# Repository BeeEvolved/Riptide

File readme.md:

```
Open Source is Intrinsic to Bitcoin
```
# The bitaxeUltra 204 Riptide
Riptide, an Ocean-themed Bitaxe.
### Future Riptide Design Goals
- LEDs around the edges to create a BitHalo effect, with the LEDs producing a blue swirl, riptide or waves effect.

bitaxe is a fully open source hardware Bitcoin ASIC miner. Ultra is the 3rd major revision of the bitaxe that now includes the BM1366 ASIC from the S19XP

## Goals
- **Standalone**: can mine directly to your pool over WiFi. No External computer needed.
- **Embedded**: low cost, low maintenance, high availability, high reliability, low power.
- **ASIC**: based on the very, very efficient BM1366 from Bitmain.
- **Versatile**: solo/pool mining, autotune power/heat/efficiency.
- **Open Source**: All design files are provided.

## Features
- **ESP32-S3-WROOM-1** wifi microcontroller on board
- **TI TPS40305** buck regulator steps down the 5V input to power the BM1366
- **Maxim DS4432U+** current DAC digitally adjusts the BM1366 core voltage from 0.04V to 2.4V
- **TI INA260** power meter measures the input voltage and current of the miner
- **Microchip EMC2101** PWM controls the fan and monitors tach output. BM1366 doesn't support die temp, but we have it placed super close to the ASIC so we can use the internal temp feature.
- 0.91" **SSD1306 OLED** I2C Display Module 

## BM1366
- The BM1366 is a undocumented SHA256 mining ASIC from Bitmain. It's used in the Antminer S19XP and the S19k Pro
- Bitmain claims the BM1366 has 0.021J/GH efficiency
- The BM1366 is available (new) for around $15 each in small quantities.
- The BM1366 has a different footprint and pinout from the BM1397 and BM1387 in previous bitaxe.
- The BM1366 appears to roll more than just the nonce on the chip. This is great news, because it allows much longer serial chains of ASICs and new work doesn't need to be sent as often.

## Current Status
- Bitaxe Ultra 204 hardware has been verified and is working nicely!
- Be sure to check the [issues](https://github.com/skot/bitaxe/issues) for known bugs, reworks and errata.
- This is an _advanced_ build! You can do it, but if you're not looking for a project, it might be best to buy one pre-assembled from one of the many sellers.

## Hardware
- Order PCBs from your favorite PCB shop, like [JLCPCB](https://jlcpcb.com), [SeeedStudio](https://www.seeedstudio.com/fusion_pcb.html), or [PCBWay](https://www.pcbway.com)
    - Gerbers are in the `Manufacturing Files` dir. PCBs are 4-layer, 6mil trace/space and 0.3mm hole compatible. 1oz outer / 0.5oz inner layer thickness works well.
    - Make sure to order stencils too. These are the "paste" layers in the gerbers folder. one for top and one for bottom.
- All PCB parts except the ASIC are available from [DigiKey](https://www.digikey.com/en/products) and others. You can find Digikey part numbers on the DK tab of the BOM
- [BM1366 ASIC from NBTC on AliExpress](https://www.aliexpress.us/item/3256804709142138.html). I got the "AG" variant. Not really sure what the difference is -- "AL" works also.
- [40x40mm heatsink and 5V fan](https://www.aliexpress.com/item/2251832861666365.html) from a random AliExpress seller. The fans are crap, but the heatsinks are good. **make sure** to use a good quality thermal compound between the heatsink and ASIC!
- Upgrade your fan with the [Noctua NF-A4x10](https://noctua.at/en/nf-a4x10-5v-pwm) 5V 4-Pin fan for a much more pleasant experience.
- Supports 0.91" SSD1306-based I2C OLED Module. [Example Amazon seller](https://www.amazon.com/gp/product/B08ZY4YBHL)
- [KiCad 7](https://www.kicad.org) design files

## Software
- The [ESP-Miner](https://github.com/skot/ESP-Miner) firmware used for the BM1397-based bitaxe has been adapted for the BM1366 and the current main branch can support both.

## Cooling
- You **must** have active cooling on the bitaxe. 
- The Bitaxe has a connector for a 5V fan. 40x40mm fans work nicely with the suggested heatsink
- The fan connector uses the 4-pin standard:
	- 2 pins are for 5V power
	- pin 3 is fan speed sensing
	- pin 4 is fan speed control (PWM) 

## Power Supply Requirements
- **5V DC Only!** Anything else will damage the Bitaxe. Be careful and double-check your power supply is 5V. Many other voltage power supplies use the same connector.
- [5VDC Power supply](https://www.amazon.com/BTF-LIGHTING-Plastic-Adapter-Transformer-WS2812B/dp/B01D8FM4N4). Should be capable of over 15W
- The bitaxe uses a 5.5x2.5mm, center-positive barrel jack.

### ESP32 Programming Requirements
- As of the bitaxeUltra, all ESP32 programming is done through a USB-C cable and connector on the bitaxe. See [ESP-Miner](https://github.com/skot/ESP-Miner) for more details.

## Building
- Check out [building.md](building.md) for PCB ordering tips
- Check out [assembly.md](assembly.md) for assembly tips

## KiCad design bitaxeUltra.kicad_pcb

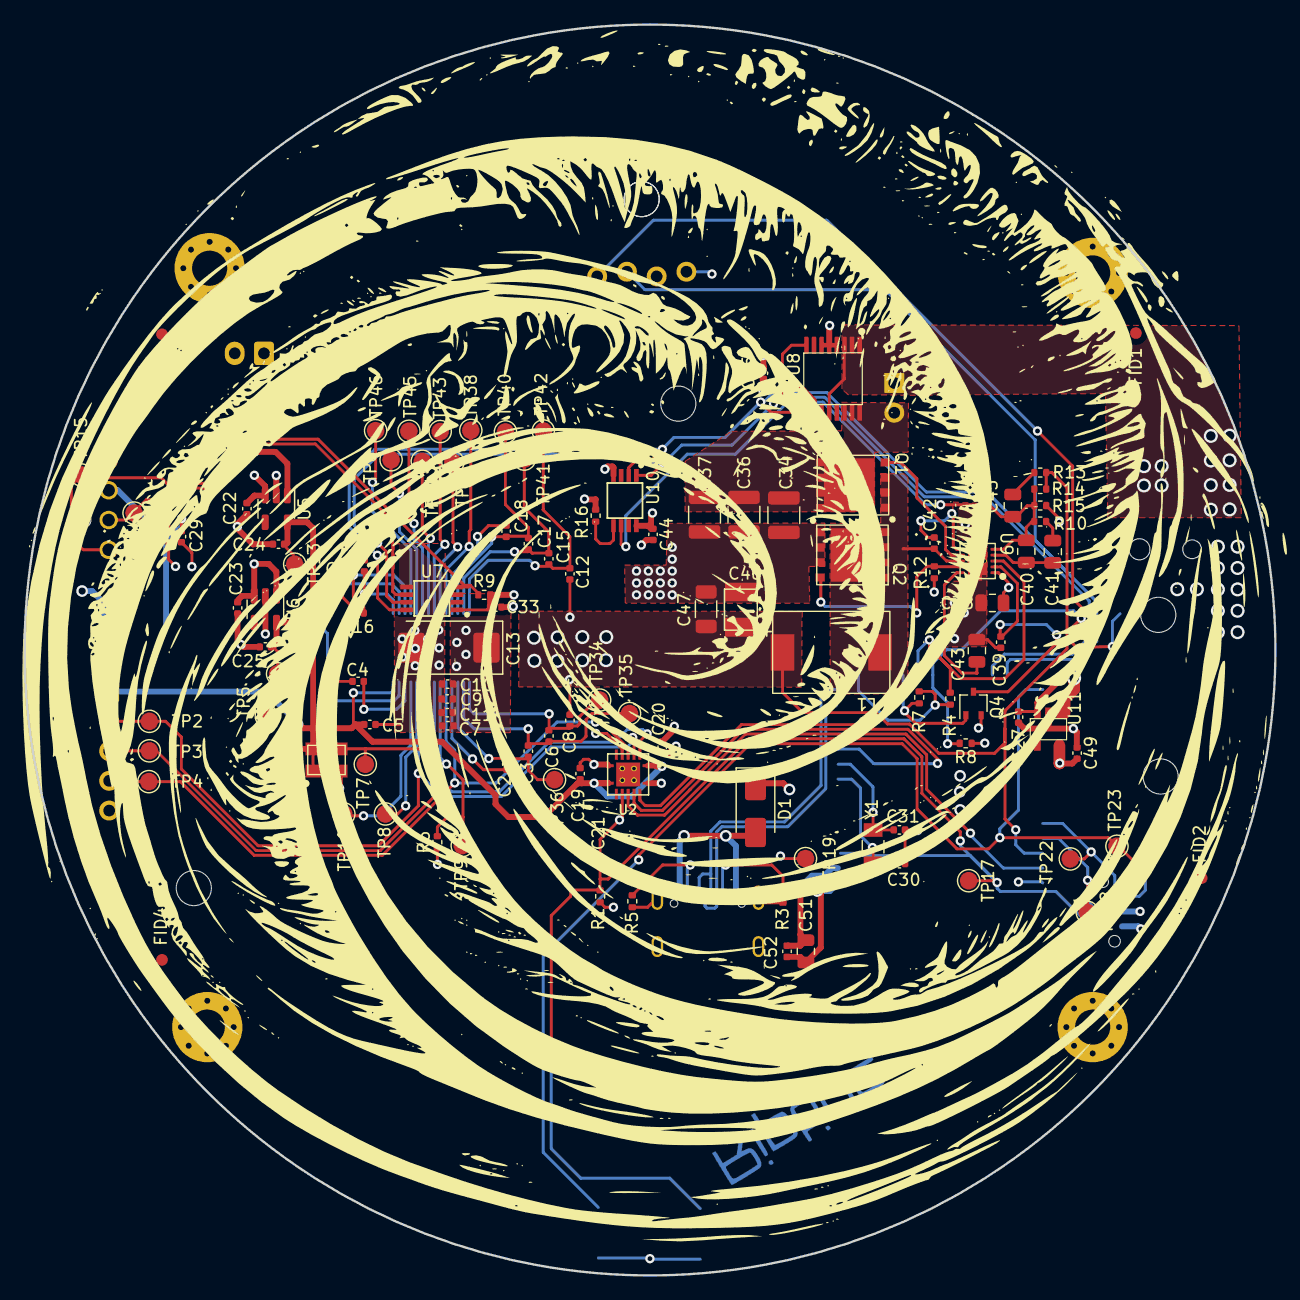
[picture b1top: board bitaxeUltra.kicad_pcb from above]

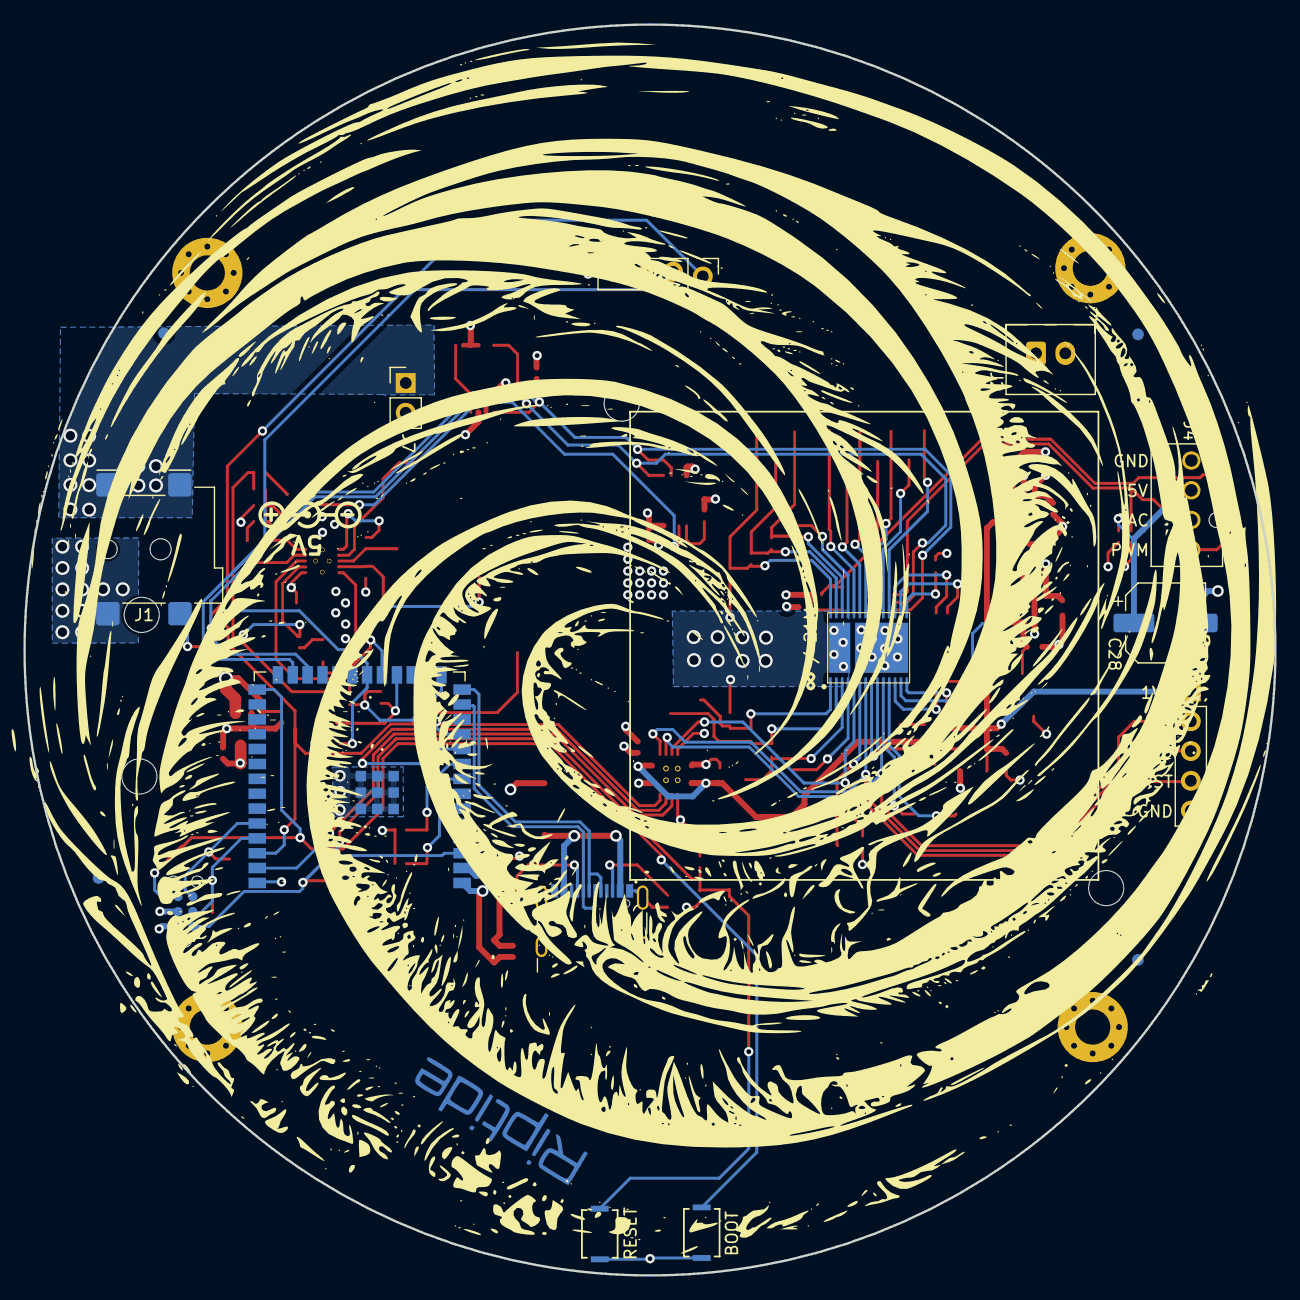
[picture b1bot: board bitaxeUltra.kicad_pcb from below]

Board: 4 copper layers, 106.8 x 106.8 mm, 135 parts (18 on the bottom side), 61 nets.

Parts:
C1, C7, C9, C19, C20, C29, C33, C42, C52: 0.1uF; C_0402_1005Metric
C2, C3, C4, C5, C6, C8, C10, C11, C12, C14, C15, C16, C17, C18, C21, C22, C23, C24, C25, C27, C35, C44, C49: 1uF; C_0402_1005Metric
C13: 330uF; CP_EIA-7343-31_Kemet-D_Pad2.25x2.55mm_HandSolder
C28: 220uF; CP_Elec_6.3x7.7
C30, C31: 6.8pF; C_0402_1005Metric
C34, C36, C37: 47uF; C_1210_3225Metric
C38: 1uF; C_0805_2012Metric
C39: 3.3nF; C_0402_1005Metric
C40: 180pF; C_0805_2012Metric
C41: 1.5nF; C_0805_2012Metric
C43, C51: 10uF; C_0805_2012Metric
C45: 470pF; C_0805_2012Metric
C46: 220uF; CAP_2R5TPE220MAFB
C47: 100uF; C_1206_3216Metric
D1: SS310; D_SMA
FID1, FID2, FID3, FID4, FID5, FID6, FID7, FID8: Fiducial; Fiducial_1mm_Mask2mm
H5, H6: MountingHole; MountingHole_3.5mm
H7, H8, H9, H10: MountingHole_Pad; MountingHole_3mm_Pad_Via
J1: 54-00164; BarrelJack_Wuerth_694106106102_2.0x5.5mm
J2: Conn_01x02; JST_XH_B2B-XH-A_1x02_P2.50mm_Vertical
J3: Conn_01x05; PinHeader_1x05_P2.54mm_Vertical
J3#2: Conn_01x04; PinHeader_1x04_P2.54mm_Vertical_shifted
J4: Conn_01x04; 470531000
J5: TC2030-IDC; Tag-Connect_TC2030-IDC-NL_2x03_P1.27mm_Vertical
J7: Conn_01x02; PinHeader_1x02_P2.54mm_Vertical
J8: USB_C_Receptacle_USB2.0; USB_C_Receptacle_GCT_USB4105-xx-A_16P_TopMnt_Horizontal
L1: 150nH; FP1005R1-R15-R
Q1, Q2: CSD17311Q5
Q4: 2N7002K; SOT-323_SC-70
R1, R4, R6, R7, R9: 10k; R_0402_1005Metric
R2: 5.6k; R_0402_1005Metric
R3, R5: 5.1k; R_0402_1005Metric
R8: 1M; R_0402_1005Metric
R10: 3.83k; R_0402_1005Metric
R12: 4.12k; R_0402_1005Metric
R13: 1.33k; R_0402_1005Metric
R14: 4.99k; R_0402_1005Metric
R15: 3.32k; R_0402_1005Metric
R16: 80.6k; R_0402_1005Metric
SW1, SW2: GT-TC029B-H025-L1N; SW_CS1213AGF260_CRS
TP1, TP2, TP3, TP4, TP5, TP6, TP7, TP8, TP9, TP10, TP13, TP14, TP15, TP16, TP17, TP18, TP19, TP22, TP23, TP34, TP35, TP36, TP38, TP40, TP41, TP42, TP43, TP44, TP45, TP46: TestPoint; TestPoint_Pad_D1.5mm
U1: 25MHz; O 25,0-JO32-B-1V3-1-T1-LF
U2: TXB0104RGYR; TXB0104
U3: polarity
U5: MCP1824T-1802E; SOT-23-5
U6: MCP1824T-0802E; SOT-23-5
U7: EMC2101; TSSOP-8_3x3mm_P0.65mm
U8: INA260; TSSOP-16_4.4x5mm_P0.65mm
U9: TPS40305
U10: DS4432U+; TSSOP-8_3x3mm_P0.65mm
U11: RT9080-33GJ5
U12: ESP32-S3-WROOM-1
U14: BM1366_mode1; BM1366
Y1: 32.768kHz; SC32S-7PF20PPM

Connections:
/3V3: C20.1, C33.1, C35.1, C44.1, C49.1, C51.1, C52.1, J3#2.3, J5.2, R1.1, R2.2, R4.1, R7.1, R8.1, R9.2, TP19.1, U2.14 (VCCB), U7.1 (VDD), U8.10 (VS), U10.8 (VCC), U11.5 (VOUT), U12.2 (3V3), U12.15 (GPIO3/TOUCH3/ADC1_CH2*)
/5V: C22.1, C23.1, C27.1, C28.1, C29.1, C34.1, C36.1, C37.1, C38.1, D1.1, J2.2, J4.2, J7.2, Q1.5 (D), U5.1 (VIN), U5.3 (EN), U6.1 (VIN), U6.3 (EN), U8.14 (IN-), U8.15 (IN-), U8.16 (IN-), U9.1 (VDD), U11.1 (VIN), U11.3 (EN)
/BM1366/0V8: C4.1, C25.1, TP14.1, U6.5 (VOUT), U14.13 (VDDIO_08_0)
/BM1366/1V8: C1.2, C5.1, C19.1, C24.1, J3.1, TP13.1, U1.1 (EN), U1.4 (VIN), U2.1 (VCCA), U2.8 (OE), U5.5 (VOUT), U14.14 (VDDIO_18_0)
/BM1366/ADDR0: TP8.1, U14.10 (ADDR0)
/BM1366/ADDR1: TP10.1, U14.11 (ADDR1)
/BM1366/BI: R6.2, TP9.1, U14.6 (BI)
/BM1366/BO: TP1.1, U14.23 (BO)
/BM1366/CI: J3.2, TP2.1, U2.3 (A2), U14.9 (CI)
/BM1366/CLKI: TP7.1, U1.3 (OUT), U14.8 (CLKI)
/BM1366/CLKO: TP44.1, U14.21 (CLKO)
/BM1366/CO: TP45.1, U14.20 (CO)
/BM1366/INV_CLKO: TP6.1, U14.19 (INV_CLKO)
/BM1366/NRSTO: TP38.1, U14.24 (NRSTO)
/BM1366/PIN_MODE: TP46.1, U14.18 (PIN_MODE)
/BM1366/RI: TP43.1, U14.22 (RI)
/BM1366/RO: J3.3, TP3.1, U2.2 (A1), U14.7 (RO)
/BM1366/RST_N: J3.4, TP4.1, U2.4 (A3), U14.5 (NRSTI)
/BM1366/VDD1_0: C6.2, C8.1, TP34.1, U14.1 (VDD1_0)
/BM1366/VDD1_1: C12.2, C15.1, TP42.1, U14.28 (VDD1_1)
/BM1366/VDD2_0: C3.2, C6.1, TP35.1, U14.2 (VDD2_0)
/BM1366/VDD2_1: C15.2, C17.1, TP41.1, U14.27 (VDD2_1)
/BM1366/VDD3_0: C2.2, C3.1, TP36.1, U14.3 (VDD3_0)
/BM1366/VDD3_1: C17.2, C18.1, TP40.1, U14.26 (VDD3_1)
/ESP32/EN: C21.1, J5.1, R1.2, SW1.2, TP17.1, U12.3 (EN)
/ESP32/IO0: J5.6, SW2.2, TP23.1, U12.27 (GPIO0/BOOT*)
/ESP32/PWR_EN: Q4.1 (G), R7.2, U12.18 (GPIO10/TOUCH10/ADC1_CH9/FSPICS0/FSPIIO4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)
/ESP32/P_RX: J5.5, TP22.1, U12.36 (U0RXD/GPIO44/CLK_OUT2)
/ESP32/P_TX: J5.3, TP18.1, U12.37 (U0TXD/GPIO43/CLK_OUT1)
/ESP32/XIN32: C30.1, U12.8 (GPIO15/U0RTS/ADC2_CH4/XTAL_32K_P), Y1.1
/ESP32/XOUT32: C31.1, U12.9 (GPIO16/U0CTS/ADC2_CH5/XTAL_32K_NH5), Y1.2
/Fan/FAN_PWM: J4.4, R9.1, TP15.1, U7.4 (FAN)
/Fan/FAN_TACH: J4.3, R2.1, TP16.1, U7.6 (ALERT/TACH)
/PLUG_SENSE: J1.3, R8.2, U12.20 (GPIO12/TOUCH12/ADC2_CH1/FSPICLK/FSPIIO6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)
/Power/OUT0: C40.2, C45.2, R10.2, R14.2, R15.1, U9.5 (FB), U10.6 (OUT0)
/Power/PGOOD: R4.2, U9.3 (PGOOD), U12.19 (GPIO11/TOUCH11/ADC2_CH0/FSPID/FSPIIO5/S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)
/Power/SW: C42.2, L1.1, Q1.1, Q1.2, Q1.3 (S), Q2.5 (D), U9.8 (SW)
/Power/VIN: J1.1, J7.1, U8.1 (IN+), U8.2 (IN+), U8.3 (IN+), U8.12 (VBUS)
/RST: U2.11 (B3), U12.39 (GPIO1/TOUCH1/ADC1_CH0)
/RX: U2.13 (B1), U12.11 (GPIO18/U1RXD/ADC2_CH7/CLK_OUT3)
/SCL: J3#2.2, U7.8 (SMCLK), U8.9 (SCL), U10.2 (SCL), U12.25 (GPIO48/SPICLK_N/SUBSPICLK_N_DIFF)
/SDA: J3#2.1, U7.7 (SMDATA), U8.8 (SDA), U10.1 (SDA), U12.24 (GPIO47/SPICLK_P/SUBSPICLK_P_DIFF)
/TX: U2.12 (B2), U12.10 (GPIO17/U1TXD/ADC2_CH6)
/VDD: C7.1, C8.2, C9.1, C10.1, C11.1, C12.1, C13.1, C46.1, C47.1, L1.2, R13.1, R14.1, U12.38 (GPIO2/TOUCH2/ADC1_CH1), U14.29 (VDD)
GND: C1.1, C2.1, C4.2, C5.2, C7.2, C9.2, C10.2, C11.2, C13.2, C14.2, C16.2, C18.2, C19.2, C20.2, C21.2, C22.2, C23.2, C24.2, C25.2, C27.2, C28.2, C29.2, C30.2, C31.2, C33.2, C34.2, C35.2, C36.2, C37.2, C38.2, C39.2, C43.2, C44.2, C46.2, C47.2, C49.2, C51.2, C52.2, H7.1, H8.1, H9.1, H10.1, J1.2, J2.1, J3.5, J3#2.4, J4.1, J5.4, J8.A1 (GND), J8.A12 (GND), J8.B1 (GND), J8.B12 (GND), J8.S1 (SHIELD), Q2.1, Q2.2, Q2.3 (S), Q4.2 (S), R3.1, R5.1, R6.1, R12.2, R15.2, R16.2, SW1.1, SW2.1, TP5.1, U1.2 (GND), U2.5 (A4), U2.7 (GND), U2.10 (B4), U2.15 (GND), U2.16 (GND), U2.17 (GND), U2.18 (GND), U2.19 (GND), U5.2 (GND), U6.2 (GND), U7.5 (GND), U8.4 (A1), U8.5 (A0), U8.6 (GND), U8.11 (GND), U9.11 (GND), U10.4 (GND), U11.2 (GND), U12.1 (GND), U12.40 (GND), U12.41 (GND), U14.4 (VSS), U14.12 (PLL_VSS), U14.17 (VSS), U14.25 (VSS), U14.30 (VSS)
unnamed: C41.2, R10.1
unnamed: C45.1, R13.2
unnamed: D1.2, J8.A4 (VBUS), J8.A9 (VBUS), J8.B4 (VBUS), J8.B9 (VBUS)
unnamed: J8.A5 (CC1), R3.2
unnamed: J8.B5 (CC2), R5.2
unnamed: Q1.4 (G), U9.7 (HDRV)
unnamed: Q2.4 (G), R12.1, U9.9 (LDRV)
unnamed: C39.1, Q4.3 (D), U9.2 (EN/SS)
unnamed: C42.1, U9.6 (BOOT)
unnamed: C43.1, U9.10 (BP)
unnamed: C40.1, C41.1, U9.4 (COMP)
unnamed: R16.1, U10.5 (FS0)
unnamed: J8.A7 (D-), J8.B7 (D-), U12.13 (GPIO19/U1RTS/ADC2_CH8/CLK_OUT2/USB_D-)
unnamed: J8.A6 (D+), J8.B6 (D+), U12.14 (GPIO20/U1CTS/ADC2_CH9/CLK_OUT1/USB_D+)
unnamed: C16.1, U14.16 (VDDIO_08_1)
unnamed: C14.1, U14.15 (VDDIO_18_1)

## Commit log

2024-08-16 Update: moved power, buttons and adapted screen for OLED Yellow and Blue Screen
    Update: moved power, buttons and adapted screen for OLED Yellow and Blue Screen
